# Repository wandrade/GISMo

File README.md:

# G.I.S.Mo

  |   | 
:-------------------------:|:-------------------------:|:-------------------------:

After a long search, I have failed to find a servo motor that does everything I need for my projects that is also cheap(ish) and fully programmable (say no to closed source stuff whenever you can).

Well, thus was born the idea of GISMo (Greatly Inteligent Servo Motor). This project aims to develop a board that can be used to replace the vanilla servo driver boards that comes with cheaper ones such as MG995 and MG996R, giving it more power and making it more usefull for distributed controll projects:

Wishlist:
- [x] Embedded MCU (STM32F302 powered!) 
- [x] Current sensing (for torque controll and power management features) 
- [ ] I2C interface (or if you please, just change a bit the circuit to use whatever interface you want)
- [x] Programable LED's (because they are cool)
- [x] Absolute magnetic encoder (at least 12bits)
- [x] Free range of movement (180 degrees is just not enough)
- [ ] Control:
    - [ ] Simple position PID loop
    - [ ] MISO controller for speed and position simultaniously (Probably a state space controller)
    - [ ] Torque controll loop
    - [ ] Trapezoidal position curve following
- [ ] Configurable parameters
    - [ ] Speed/Position/Current limit
    - [ ] Controller mode
    - [ ] Configurable break zone (turn on break when position reaches its demand and settles)
    - [ ] Multiturn counter
    - [ ] Controller gains (PID and state space gain matrix)
- [ ] ROS2 Interface node:
    - [ ] Hot plug I2C device detection
    - [ ] Configuration via YAML and ROS Param
    - [ ] up to 16 Individually addressed servos

# Organization
The project contains 3 main blocks: first is the hardware, using [KiCad](https://kicad-pcb.org/), in the Hardware folder you will find 2 subfolders, one for the dev board, which is a big version of the board with some more stuff to facilitate firmware development and debugging, and a second one that contains the GISMo board that actually fits in the servo (to be made).
Then we have the Firmware with two other bits, the [CubeMX](https://www.st.com/en/development-tools/stm32cubemx.html) project so we have everything neatly initialized in our MCU, and the actual firmware and its libs.

# Version History
Now this is a bit tricky. I have 3 things to version and no interest in havving 3 different repos for them at all, so ill trake and make it sensible.

Each sub-thing will have its own sub-version, and once I have a combination of the 3 of them that kind of works, I will merge it into the master branch and tag it with a overall version of the repo (if that makes sense).

## Firmware
--

## GISMo Board
- [Interactive BOM](http://htmlpreview.github.io/?https://github.com/wandrade/GISMo/blob/develop/Hardware/GISMoBoard/bom/ibom.html)

 | 
:-------------------------:|:-------------------------:
- 0.0.1 - Copy of dev board with a few changes to reduce space usage
    - Only one I2C/Power plug
    - Replaced Address header pins by solder jumpers
    - Motor and PWM sensor connectors replaced with solder pads
    - Included a heat sink pad under the motor driver
    - Removed Crystal and oscilator
    - Reduced LED packages
    - Removed Debug connector
    - Removed reset button

## Development Board
- [Interactive BOM](http://htmlpreview.github.io/?https://github.com/wandrade/GISMo/blob/develop/Hardware/DevBoard/bom/ibom.html)

This board is meant for circuit testing and ease of debugging.

- 0.0.1 - Initial proposal board for development board schematic and layout.
    - [STM32F302K8 MCU](https://www.st.com/en/microcontrollers-microprocessors/stm32f302k8.html) - Small package and seemingly enough processing power for everything we need.
    - [DRV8876RGTR Driver](https://www.ti.com/store/ti/en/p/product/?p=DRV8876RGTR) - Has more than double the current needed and provides an inbuilt current sensing solution (hopefully good enough)

# Costs
Here I will keep track of how much you have to pay for each of the more expensive bits so you have an idea of how much a working GISMo will cost you.

# FAQ
I have barely started this project and everytime I tell somebody about it, I get the same questions, so here we go:

- Why not use a normal DC motor with drivers tailored for each project:
    - Cause I like modular! It saves time and you dont have to do everything multiple times. Plus, a lot of the stuf you find online if you are 3D printing, is already made for this size motor. Plus Plus, sorting out motor specifications, gearboxes, making gears (when necessary) is all just a pain, this one can do a lot of the stuff I need for anyway (robotic arms and legged robots).

- Why not just buy a smart servo? this one will probably cost almost the same as the comercial ones.
    - For one, i Hope to make it at least the same price as the "cheap" smart servos. But really, mainly, so I can have full power over its features and its firmware. Also cause its fun!

For now that is it, lets see what comes next :)

# License
Everything under this repository is free to use unless it is used to generate profit. The license states that it CAN be used for comercial puproses, however an agreement have to be reached between the original creator of this project (Werner Thomassen Andrade) and the interested parties before that can happens.

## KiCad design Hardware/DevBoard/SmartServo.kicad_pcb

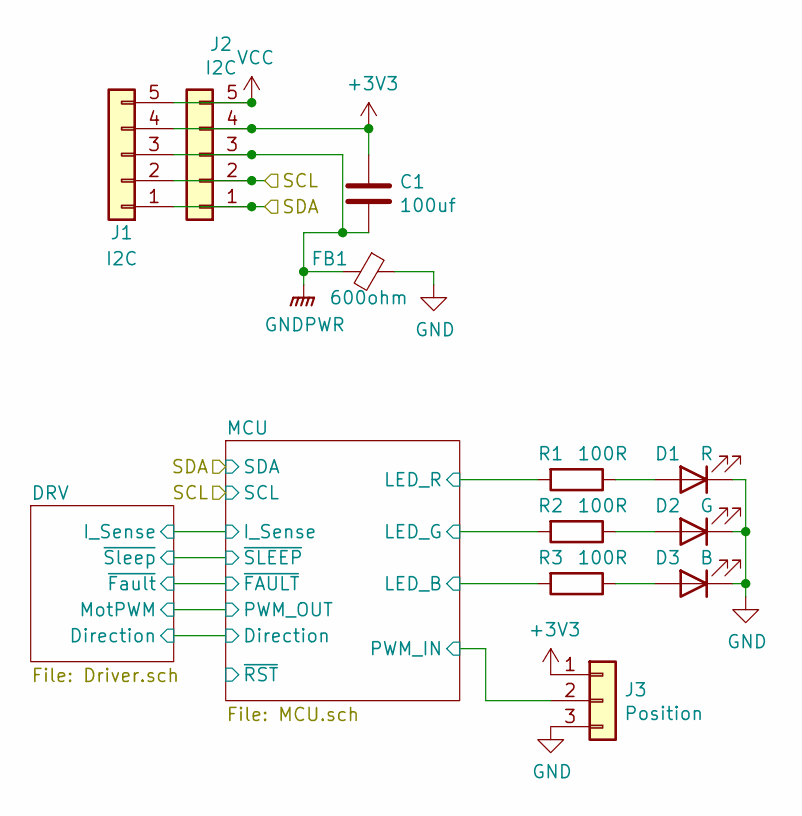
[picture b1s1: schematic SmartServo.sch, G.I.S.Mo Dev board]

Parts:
C1: 100uf; C_0603_1608Metric
D1: R; LED_1210_3225Metric
D2: G; LED_1210_3225Metric
D3: B; LED_1210_3225Metric
FB1: 600ohm; R_0603_1608Metric
J1, J2: I2C; JST_PH_B5B-PH-K_1x05_P2.00mm_Vertical
J3: Position; JST_PH_B3B-PH-K_1x03_P2.00mm_Vertical
R1, R2, R3: 100R; R_0603_1608Metric

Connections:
+3V3: C1.1, J1.4, J2.4, J3.1; also elsewhere on the board
/MCU/LED_B: R3.2; also elsewhere on the board
/MCU/LED_G: R2.2; also elsewhere on the board
/MCU/LED_R: R1.2; also elsewhere on the board
/MCU/PWM_IN: J3.2; also elsewhere on the board
/SCL: J1.2, J2.2; also elsewhere on the board
/SDA: J1.1, J2.1; also elsewhere on the board
GND: D1.1 (K), D2.1 (K), D3.1 (K), FB1.1, J3.3; also elsewhere on the board
GNDPWR: C1.2, FB1.2, J1.3, J2.3; also elsewhere on the board
unnamed: D1.2 (A), R1.1
unnamed: D2.2 (A), R2.1
unnamed: D3.2 (A), R3.1
VCC: J1.5, J2.5; also elsewhere on the board

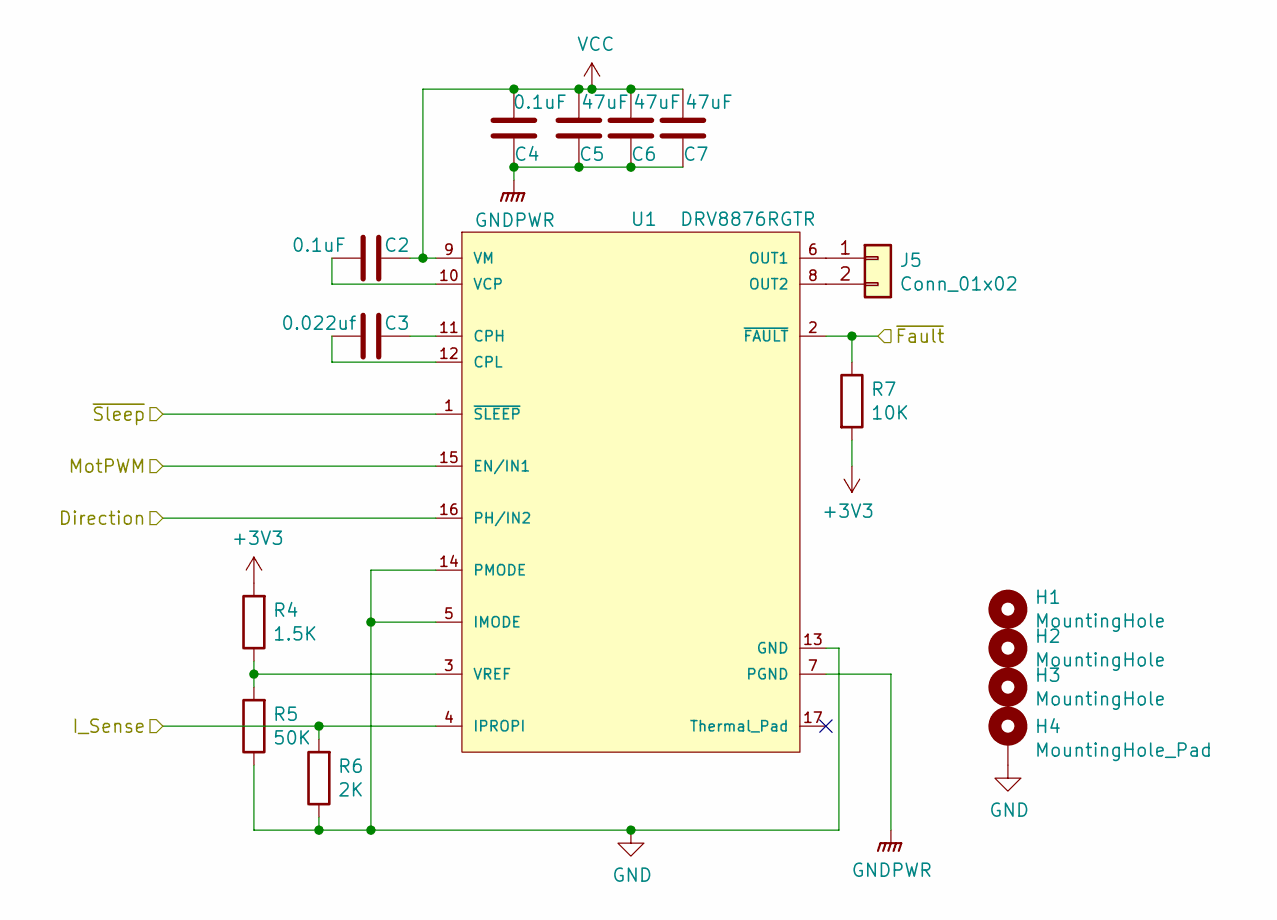
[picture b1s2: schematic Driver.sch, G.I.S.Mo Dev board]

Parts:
C2, C4: 0.1uF; C_0603_1608Metric
C3: 0.022uf; C_0603_1608Metric
C5, C6, C7: 47uF; C_1206_3216Metric; Farnell https://uk.farnell.com/tdk/c3216x5r1e47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
H1, H2, H3: MountingHole; MountingHole_3.2mm_M3
H4: MountingHole_Pad; MountingHole_3.2mm_M3_DIN965_Pad
J5: Conn_01x02; JST_PH_B2B-PH-K_1x02_P2.00mm_Vertical
R4: 1.5K; R_0603_1608Metric
R5: 50K; R_0603_1608Metric
R6: 2K; R_0603_1608Metric
R7: 10K; R_0603_1608Metric
U1: DRV8876RGTR; Texas_Instruments-RGT0016C-0-0-MFG; mouser part number 595-DRV8876RGTR

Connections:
+3V3: R4.2, R7.2; also elsewhere on the board
/DRV/Direction: U1.16 (PH/IN2); also elsewhere on the board
/DRV/I_Sense: R6.2, U1.4 (IPROPI); also elsewhere on the board
/DRV/MotPWM: U1.15 (EN/IN1); also elsewhere on the board
/MCU/~FAULT: R7.1, U1.2 (~FAULT~); also elsewhere on the board
/MCU/~SLEEP: U1.1 (~SLEEP~); also elsewhere on the board
GND: H4.1, R5.1, R6.1, U1.5 (IMODE), U1.13 (GND), U1.14 (PMODE); also elsewhere on the board
GNDPWR: C4.1, C5.1, C6.1, C7.1, U1.7 (PGND); also elsewhere on the board
unnamed: C2.2, U1.10 (VCP)
unnamed: C3.1, U1.11 (CPH)
unnamed: C3.2, U1.12 (CPL)
unnamed: J5.1, U1.6 (OUT1)
unnamed: J5.2, U1.8 (OUT2)
unnamed: R4.1, R5.2, U1.3 (VREF)
VCC: C2.1, C4.2, C5.2, C6.2, C7.2, U1.9 (VM); also elsewhere on the board

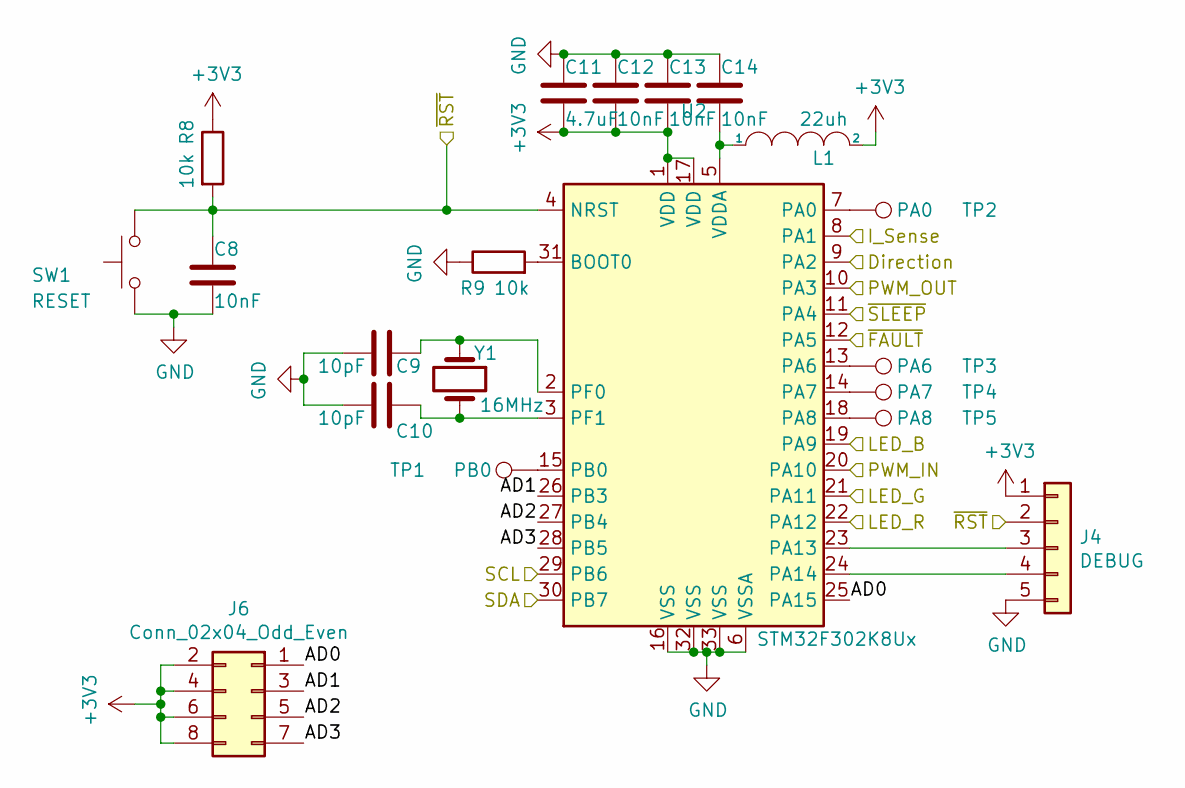
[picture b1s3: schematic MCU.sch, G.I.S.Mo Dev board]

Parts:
C8, C12, C13, C14: 10nF; C_0603_1608Metric
C9, C10: 10pF; C_0603_1608Metric
C11: 4.7uF; C_0603_1608Metric
J4: DEBUG; JST_PH_B5B-PH-K_1x05_P2.00mm_Vertical
J6: Conn_02x04_Odd_Even; PinHeader_2x04_P2.54mm_Vertical
L1: 22uh; L_0603_1608Metric
R8, R9: 10k; R_0603_1608Metric
SW1: RESET; SW_SPST_B3U-1000P
TP1: PB0; TestPoint_Pad_1.0x1.0mm
TP2: PA0; TestPoint_Pad_1.0x1.0mm
TP3: PA6; TestPoint_Pad_1.0x1.0mm
TP4: PA7; TestPoint_Pad_1.0x1.0mm
TP5: PA8; TestPoint_Pad_1.0x1.0mm
U2: STM32F302K8Ux; QFN-32-1EP_5x5mm_P0.5mm_EP3.45x3.45mm
Y1: 16MHz; Crystal_SMD_ECS_CSM3X-2Pin_7.6x4.1mm

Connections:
+3V3: C11.2, C12.2, C13.2, J4.1, J6.2, J6.4, J6.6, J6.8, L1.2, R8.1, U2.1 (VDD), U2.17 (VDD); also elsewhere on the board
/DRV/Direction: U2.9 (PA2); also elsewhere on the board
/DRV/I_Sense: U2.8 (PA1); also elsewhere on the board
/DRV/MotPWM: U2.10 (PA3); also elsewhere on the board
/MCU/AD0: J6.1, U2.25 (PA15)
/MCU/AD1: J6.3, U2.26 (PB3)
/MCU/AD2: J6.5, U2.27 (PB4)
/MCU/AD3: J6.7, U2.28 (PB5)
/MCU/LED_B: U2.19 (PA9); also elsewhere on the board
/MCU/LED_G: U2.21 (PA11); also elsewhere on the board
/MCU/LED_R: U2.22 (PA12); also elsewhere on the board
/MCU/PWM_IN: U2.20 (PA10); also elsewhere on the board
/MCU/~FAULT: U2.12 (PA5); also elsewhere on the board
/MCU/~RST: C8.1, J4.2, R8.2, SW1.2, U2.4 (NRST)
/MCU/~SLEEP: U2.11 (PA4); also elsewhere on the board
/SCL: U2.29 (PB6); also elsewhere on the board
/SDA: U2.30 (PB7); also elsewhere on the board
GND: C8.2, C9.2, C10.2, C11.1, C12.1, C13.1, C14.1, J4.5, R9.1, SW1.1, U2.6 (VSSA), U2.16 (VSS), U2.32 (VSS), U2.33 (VSS); also elsewhere on the board
unnamed: C9.1, U2.2 (PF0), Y1.1
unnamed: C10.1, U2.3 (PF1), Y1.2
unnamed: C14.2, L1.1, U2.5 (VDDA)
unnamed: J4.3, U2.23 (PA13)
unnamed: J4.4, U2.24 (PA14)
unnamed: R9.2, U2.31 (BOOT0)
unnamed: TP1.1, U2.15 (PB0)
unnamed: TP2.1, U2.7 (PA0)
unnamed: TP3.1, U2.13 (PA6)
unnamed: TP4.1, U2.14 (PA7)
unnamed: TP5.1, U2.18 (PA8)

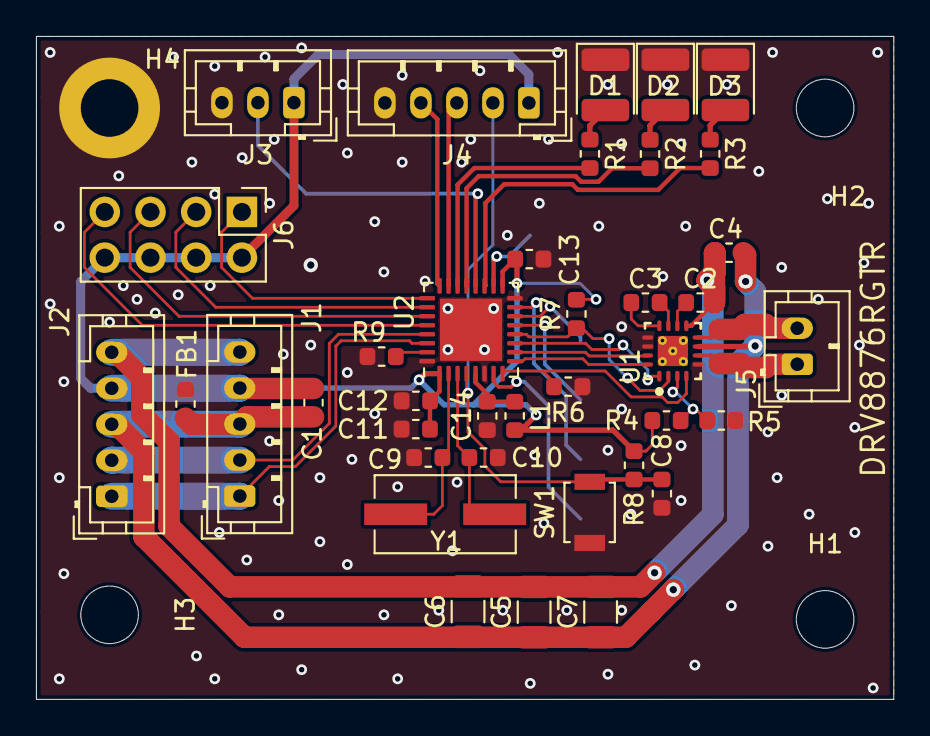
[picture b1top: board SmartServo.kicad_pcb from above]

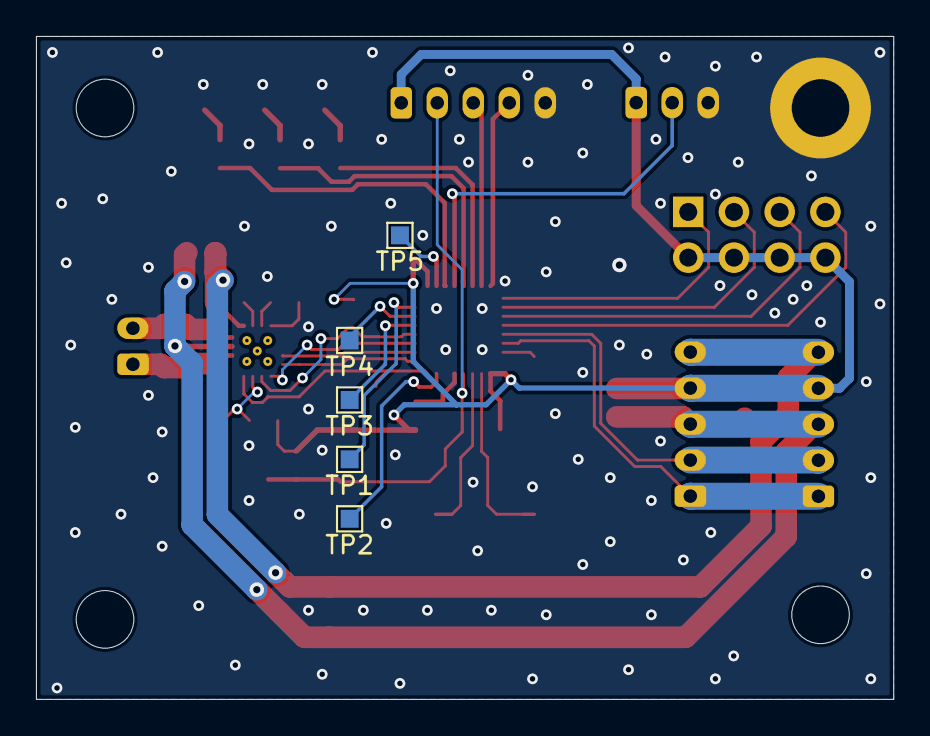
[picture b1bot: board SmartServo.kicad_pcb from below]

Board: 2 copper layers, 47.6 x 36.8 mm, 47 parts (5 on the bottom side), 40 nets.

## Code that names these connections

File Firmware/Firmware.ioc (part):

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Mcu.Name=STM32F302K(6-8)Ux
Mcu.Package=UFQFPN32
Mcu.UserName=STM32F302K8Ux
PA0.GPIOParameters=GPIO_Speed,GPIO_PuPd,GPIO_Label
PA0.GPIO_Label=DEBUG_1
PA0.GPIO_PuPd=GPIO_PULLDOWN
PA0.GPIO_Speed=GPIO_SPEED_FREQ_HIGH
PA0.Signal=GPIO_Output
PA1.GPIOParameters=GPIO_Label
PA1.GPIO_Label=I_Sense
PA1.Mode=IN2-Single-Ended
PA1.Signal=ADC1_IN2
PA10.GPIOParameters=GPIO_Label
PA10.GPIO_Label=PWM_IN
PA10.Signal=S_TIM1_CH3
PA11.GPIOParameters=GPIO_Label
PA11.GPIO_Label=LED_G
PA11.Signal=GPIO_Output
PA12.GPIOParameters=GPIO_Label
PA12.GPIO_Label=LED_R
PA12.Signal=GPIO_Output
PA13.Mode=Serial_Wire
PA13.Signal=SYS_JTMS-SWDIO
PA14.Mode=Serial_Wire
PA14.Signal=SYS_JTCK-SWCLK
PA15.GPIOParameters=GPIO_PuPd,GPIO_Label
PA15.GPIO_Label=AD0
PA15.GPIO_PuPd=GPIO_PULLDOWN
PA15.Signal=GPIO_Input
PA2.GPIOParameters=GPIO_Label
PA2.GPIO_Label=Direction
PA2.Signal=GPIO_Output
PA3.GPIOParameters=GPIO_Label
PA3.GPIO_Label=PWM_Out
PA3.Signal=S_TIM2_CH4
PA4.GPIOParameters=GPIO_PuPd,GPIO_Label
PA4.GPIO_Label=nSleep
PA4.GPIO_PuPd=GPIO_PULLDOWN
PA4.Signal=GPIO_Output
PA5.GPIOParameters=GPIO_Label
PA5.GPIO_Label=nFault
PA5.Signal=GPIO_Input
PA6.GPIOParameters=GPIO_Speed,GPIO_PuPd,GPIO_Label
PA6.GPIO_Label=DEBUG_2
PA6.GPIO_PuPd=GPIO_PULLDOWN
PA6.GPIO_Speed=GPIO_SPEED_FREQ_HIGH
PA6.Signal=GPIO_Output
PA7.GPIOParameters=GPIO_Speed,GPIO_PuPd,GPIO_Label
PA7.GPIO_Label=DEBUG_3
PA7.GPIO_PuPd=GPIO_PULLDOWN
PA7.GPIO_Speed=GPIO_SPEED_FREQ_HIGH
PA7.Signal=GPIO_Output
PA8.GPIOParameters=GPIO_Speed,GPIO_PuPd,GPIO_Label
PA8.GPIO_Label=DEBUG_5
PA8.GPIO_PuPd=GPIO_PULLDOWN
PA8.GPIO_Speed=GPIO_SPEED_FREQ_HIGH
PA8.Signal=GPIO_Output
PA9.GPIOParameters=GPIO_Label
PA9.GPIO_Label=LED_B
PA9.Signal=GPIO_Output
PB0.GPIOParameters=GPIO_Speed,GPIO_PuPd,GPIO_Label
PB0.GPIO_Label=DEBUG_4
PB0.GPIO_PuPd=GPIO_PULLDOWN
PB0.GPIO_Speed=GPIO_SPEED_FREQ_HIGH
PB0.Signal=GPIO_Output
PB3.GPIOParameters=GPIO_PuPd,GPIO_Label
PB3.GPIO_Label=AD1
PB3.GPIO_PuPd=GPIO_PULLDOWN
PB3.Signal=GPIO_Input
PB4.GPIOParameters=GPIO_PuPd,GPIO_Label
PB4.GPIO_Label=AD2
PB4.GPIO_PuPd=GPIO_PULLDOWN
PB4.Signal=GPIO_Input
PB5.GPIOParameters=GPIO_PuPd,GPIO_Label
PB5.GPIO_Label=AD3
PB5.GPIO_PuPd=GPIO_PULLDOWN
PB5.Signal=GPIO_Input
PB6.GPIOParameters=GPIO_Pu
PB6.GPIO_Pu=GPIO_NOPULL
PB6.Mode=I2C
PB6.Signal=I2C1_SCL
PB7.GPIOParameters=GPIO_Pu
PB7.GPIO_Pu=GPIO_NOPULL
PB7.Mode=I2C
PB7.Signal=I2C1_SDA
RCC.HSEPLLFreq_Value=8000000
RCC.HSE_VALUE=8000000
RCC.SYSCLKFreq_VALUE=64000000
RCC.SYSCLKSourceVirtual=RCC_SYSCLKSOURCE_PLLCLK
board=custom

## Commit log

2020-09-05 Create LICENSE
2020-09-05 Updated README with project description and some stuff
2020-09-05 Dev board created
2020-09-05 OCD on README.md
2020-09-06 G.I.S.Mo Board
    Mini board first release candidate
2020-09-06 Added head sink for motor driver
2020-09-07 Interactive BOM
2020-09-07 Added renders and backlid model
2020-09-10 Added images do README.md and
2020-09-10 3D printable backlid with LED and connectors slot
2020-09-10 Removed spaces from file names
2020-09-10 Fixed image path
2020-09-10 Made wishlist into checklist
2020-09-12 FW - Blink LED
2020-09-12 FW - FreeRTOS
2020-09-12 Ignore debug and release folders
2020-09-12 FW - Blink with freertos
2020-09-13 Position sensor reading
2020-09-13 FW - Speed estimation
    Its extremely noisy, could improve if period is measured instead of using fixed value
2020-09-13 FW - Spike filter on multiturn
    WTF is happening? why doenst it work? u.u
2020-09-14 FW - Bug found
    Still not happy with the position reading tho, will work more on that to make it more robust.
2020-09-14 FW - Proper position encoder reading with no unexpected values
2020-09-15 Explanation of the encoder reading stuff
    Also commented out stuff that I will continue implement later on
2020-09-16 FW - Increased encoder interrupt priority above freeRTOS
2020-09-16 Created driver functions files
2020-09-16 FW - PWM output configured
    Also moved encoder interrupt stuff to encoder.c
2020-09-16 FW - Enable/Disable motor function and some other adjustments
2020-09-17 Initial config for ADC
2020-09-17 Configured output debug pins
    For use with external analyzer
2020-09-20 FW - Output debug signal
2020-09-20 ADC on timer and DMA
2020-09-27 FW - Software ADC reading
2020-09-27 FW - ADC on timer event out
2020-09-28 FW - 4KHz current reading
2020-09-28 FW - ADC Scalar
2020-10-05 FW - Clock counter helper function
2021-09-26 Update README.md
    Added link for I²C info
2021-10-02 Separated peripherals into files and added I2C slave addressing
2021-10-02 I2C Broadcast ID
2021-10-09 New I2C reference link
2021-10-14 Basic register based I2C protocol
    Only receives/writes to a buffer
2022-09-22 Read register in I2C implemented
2022-10-22 Register setup for reading values over I2C
2022-10-22 FW - Included basic OS based LED PWM driver
2022-10-24 FW - I2C works for both read and write
2024-02-01 I2C more generic
2024-02-08 FINALLY settled on I2C schema, previous one was shite
2024-02-08 LED being controlled by I2C
2024-02-08 I2C nostrech
2024-03-22 some cleanupo
2024-03-22 So far so good
2024-03-22 Data changed
2024-09-14 Basic position PID controller
2024-09-15 Basic interface controlling position loop
2024-09-15 Script to parse data.h adding the registers offset and json for doc
2024-09-15 Configured Make and vscode in linux
2024-09-15 build clean and flash buttons for the project in vscode
2024-09-17 Necessary vscode extensions
2024-09-17 Refactor gitignore and file paths
2024-09-17 Some more vscode config
2024-09-17 Improved controler options and exposed ginas to I2C interface
2024-09-17 Improved pre build script
2024-09-17 Version file, data and hash on build
2024-09-17 Process hash before processing the rest of the file to avoid fake dirty marks
2024-09-17 Only get repo dirty then procees as normal
2024-09-17 Clean commit_hash variable (should be kept like this)
